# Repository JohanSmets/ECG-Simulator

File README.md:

# ECG-Simulator
 Electronics, Software and 3D Printable Enclosure of the ECG Patient Simulator based on an Atmega328.
 The simulator has 8 selectable heartrates going from 30 to 240 Bpm.  Works with a 9V battery and has an auto power off function.  This project consists of a Full KiCad project with schematic and PCB,  an Arduino sketch and all the 3D-printable files to make an enclosure.

 This project is licensed under Creative Commons Attribution Share-Alike International Licence 4.0

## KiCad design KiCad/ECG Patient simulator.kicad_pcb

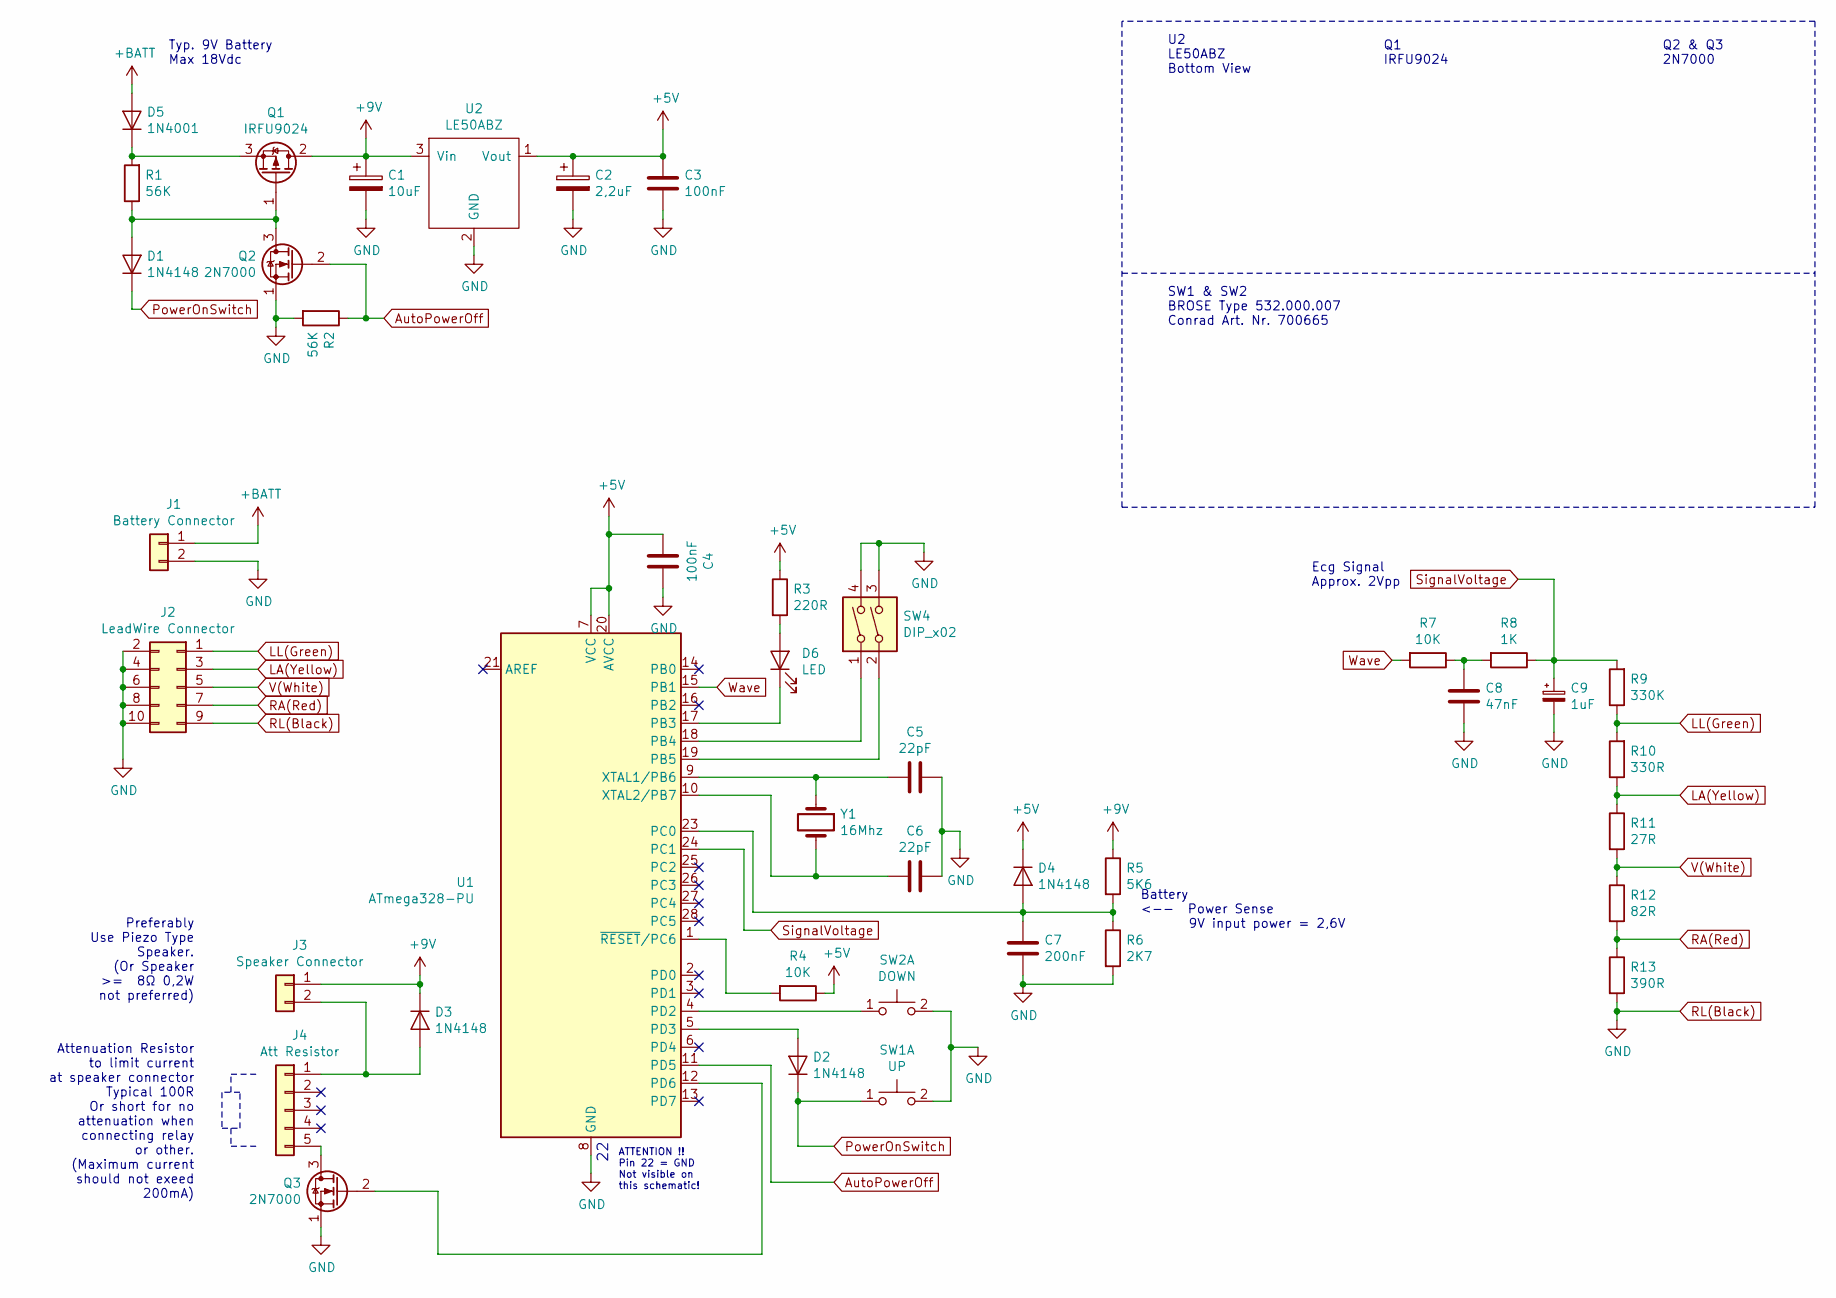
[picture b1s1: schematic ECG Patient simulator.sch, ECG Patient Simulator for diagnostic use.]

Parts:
C1: 10uF; CP_Radial_D6.3mm_P2.50mm
C2: 2,2uF; CP_Radial_D6.3mm_P2.50mm
C3, C4: 100nF; C_Disc_D5.0mm_W2.5mm_P5.00mm
C5, C6: 22pF; C_Disc_D5.0mm_W2.5mm_P5.00mm
C7: 200nF; C_Disc_D5.0mm_W2.5mm_P5.00mm
C8: 47nF; C_Disc_D5.0mm_W2.5mm_P5.00mm
C9: 1uF; CP_Radial_D6.3mm_P2.50mm
D1, D2, D3, D4: 1N4148; D_DO-35_SOD27_P7.62mm_Horizontal
D5: 1N4001; D_DO-41_SOD81_P10.16mm_Horizontal
D6: LED; LED_D5.0mm
J1: Battery Connector; PinHeader_1x02_P2.54mm_Vertical
J2: LeadWire Connector; PinSocket_2x05_P2.54mm_Vertical
J3: Speaker Connector; PinHeader_1x02_P2.54mm_Vertical
J4: Att Resistor; PinHeader_1x05_P2.54mm_Vertical
Q1: IRFU9024; TO-251-3_Vertical
Q2, Q3: 2N7000; TO-92_Inline
R1, R2: 56K; R_Axial_DIN0207_L6.3mm_D2.5mm_P10.16mm_Horizontal
R3: 220R; R_Axial_DIN0207_L6.3mm_D2.5mm_P10.16mm_Horizontal
R4, R7: 10K; R_Axial_DIN0207_L6.3mm_D2.5mm_P10.16mm_Horizontal
R5: 5K6; R_Axial_DIN0207_L6.3mm_D2.5mm_P10.16mm_Horizontal
R6: 2K7; R_Axial_DIN0207_L6.3mm_D2.5mm_P10.16mm_Horizontal
R8: 1K; R_Axial_DIN0207_L6.3mm_D2.5mm_P10.16mm_Horizontal
R9: 330K; R_Axial_DIN0207_L6.3mm_D2.5mm_P10.16mm_Horizontal
R10: 330R; R_Axial_DIN0207_L6.3mm_D2.5mm_P10.16mm_Horizontal
R11: 27R; R_Axial_DIN0207_L6.3mm_D2.5mm_P10.16mm_Horizontal
R12: 82R; R_Axial_DIN0207_L6.3mm_D2.5mm_P10.16mm_Horizontal
R13: 390R; R_Axial_DIN0207_L6.3mm_D2.5mm_P10.16mm_Horizontal
SW1: UP; Push_E-Switch_KS01Q01
SW2: DOWN; Push_E-Switch_KS01Q01
SW4: DIP_x02; DIP-4_W7.62mm
U1: ATmega328-PU; DIP-28_W7.62mm
U2: LE50ABZ; TO-92_Inline_Wide
Y1: 16Mhz; Crystal_HC18-U_Vertical

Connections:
+5V: C2.1, C3.1, C4.2, D4.1 (K), R3.1, R4.1, U1.7 (VCC), U1.20 (AVCC), U2.1 (Vout)
+9V: C1.1, D3.1 (K), J3.1, Q1.2 (D), R5.1, U2.3 (Vin); also elsewhere on the board
+BATT: D5.2 (A), J1.1; also elsewhere on the board
AutoPowerOff: Q2.2 (G), R2.1, U1.11 (PD5)
LA(Yellow): J2.3, R10.1, R11.1
LL(Green): J2.1, R9.1, R10.2
unnamed: C5.2, U1.9 (XTAL1/PB6), Y1.1
unnamed: C6.2, U1.10 (XTAL2/PB7), Y1.2
unnamed: C7.1, D4.2 (A), R5.2, R6.1, U1.23 (PC0)
unnamed: C8.1, R7.1, R8.2
unnamed: D1.2 (A), Q1.1 (G), Q2.3 (D), R1.1
unnamed: D2.2 (A), U1.5 (PD3)
unnamed 12: D3.2 (A), J3.2, J4.1; also elsewhere on the board
unnamed: D5.1 (K), Q1.3 (S), R1.2
unnamed: D6.1 (K), U1.17 (PB3)
unnamed: D6.2 (A), R3.2
unnamed: J4.5, Q3.3 (D)
unnamed: Q3.2 (G), U1.12 (PD6)
unnamed: R4.2, U1.1 (~RESET~/PC6)
unnamed: SW2.1 (C), U1.4 (PD2)
unnamed: SW4.1, U1.18 (PB4)
unnamed: SW4.2, U1.19 (PB5)
PowerOnSwitch: D1.1 (K), D2.1 (K), SW1.1 (C)
RA(Red): J2.7, R12.2, R13.1
RL(Black): C1.2, C2.2, C3.2, C4.1, C5.1, C6.1, C7.2, C8.2, C9.2, J1.2, J2.2, J2.4, J2.6, J2.8, J2.9, J2.10, Q2.1 (S), Q3.1 (S), R2.2, R6.2, R13.2, SW1.2 (D), SW2.2 (D), SW4.3, SW4.4, U1.8 (GND), U1.22 (GND), U2.2 (GND); also elsewhere on the board
SignalVoltage: C9.1, R8.1, R9.2, U1.24 (PC1)
V(White): J2.5, R11.2, R12.1
Wave: R7.2, U1.15 (PB1)

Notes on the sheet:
Battery <-- Power Sense 9V input power = 2,6V
Typ. 9V Battery Max 18Vdc
U2 LE50ABZ Bottom View
Q1 IRFU9024
Q2 & Q3 2N7000
SW1 & SW2 BROSE Type 532.000.007 Conrad Art. Nr. 700665
ATTENTION !! Pin 22 = GND Not visible on this schematic!
Ecg Signal Approx. 2Vpp
Preferably Use Piezo Type Speaker. (Or Speaker >= 8Ω 0,2W not preferred)
Attenuation Resistor to limit current at speaker connector Typical 100R Or short for no attenuation when connecting relay or other. (Maximum current should not exeed 200mA)

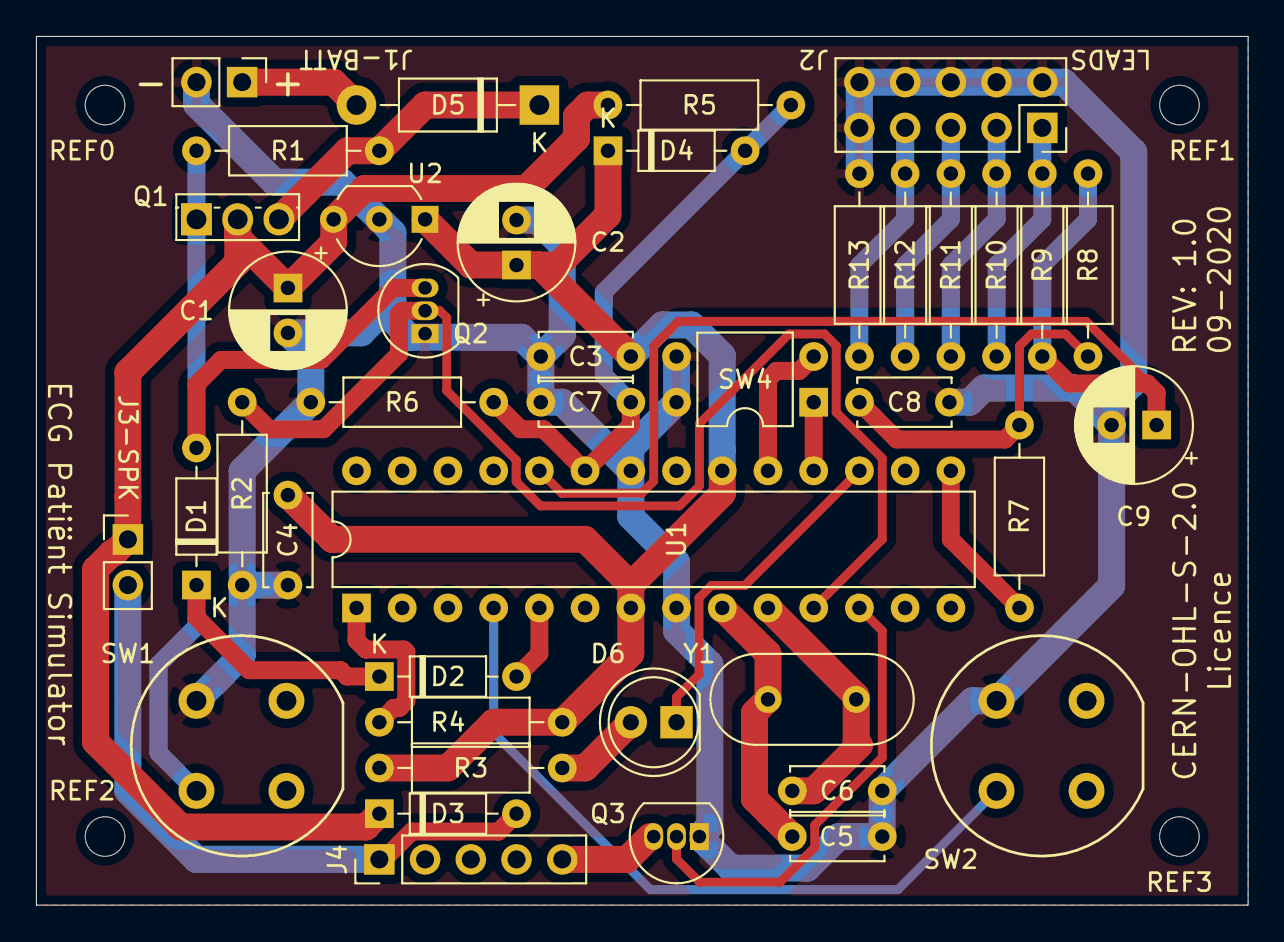
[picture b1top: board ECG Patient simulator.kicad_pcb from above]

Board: 2 copper layers, 67.3 x 48.3 mm, 45 parts (0 on the bottom side), 28 nets.

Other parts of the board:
J1-BATT: Battery Connector; PinHeader_1x02_P2.54mm_Vertical
J3-SPK: Speaker Connector; PinHeader_1x02_P2.54mm_Vertical
REF0, REF1, REF2, REF3: MountingHole_2.2mm_M2_ISO7380

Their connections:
+9V: J3-SPK.1; also elsewhere on the board
+BATT: J1-BATT.1; also elsewhere on the board
unnamed 12: J3-SPK.2; also elsewhere on the board
RL(Black): J1-BATT.2; also elsewhere on the board

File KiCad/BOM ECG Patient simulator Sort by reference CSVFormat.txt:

"Source:","C:\Users\Johan\Documents\Arduino\Projecten\ECG Simulator\KiCad ECG Patient simulator\ECG Patient simulator.sch"
"Date:","14/11/2020 13:45:55"
"Tool:","Eeschema (5.1.0)-1"
"Component Count:","41"
"Ref","Value","Footprint","Datasheet","Manufacturer","Vendor"
"C1","10uF","Capacitor_THT:CP_Radial_D6.3mm_P2.50mm","~","",""
"C2","2,2uF","Capacitor_THT:CP_Radial_D6.3mm_P2.50mm","~","",""
"C3","100nF","Capacitor_THT:C_Disc_D5.0mm_W2.5mm_P5.00mm","~","",""
"C4","100nF","Capacitor_THT:C_Disc_D5.0mm_W2.5mm_P5.00mm","~","",""
"C5","22pF","Capacitor_THT:C_Disc_D5.0mm_W2.5mm_P5.00mm","~","",""
"C6","22pF","Capacitor_THT:C_Disc_D5.0mm_W2.5mm_P5.00mm","~","",""
"C7","200nF","Capacitor_THT:C_Disc_D5.0mm_W2.5mm_P5.00mm","~","",""
"C8","47nF","Capacitor_THT:C_Disc_D5.0mm_W2.5mm_P5.00mm","~","",""
"C9","1uF","Capacitor_THT:CP_Radial_D6.3mm_P2.50mm","~","",""
"D1","1N4148","Diode_THT:D_DO-35_SOD27_P7.62mm_Horizontal","https://assets.nexperia.com/documents/data-sheet/1N4148_1N4448.pdf","",""
"D2","1N4148","Diode_THT:D_DO-35_SOD27_P7.62mm_Horizontal","https://assets.nexperia.com/documents/data-sheet/1N4148_1N4448.pdf","",""
"D3","1N4148","Diode_THT:D_DO-35_SOD27_P7.62mm_Horizontal","~","",""
"D4","1N4148","Diode_THT:D_DO-35_SOD27_P7.62mm_Horizontal","https://assets.nexperia.com/documents/data-sheet/1N4148_1N4448.pdf","",""
"D5","1N4001","Diode_THT:D_DO-41_SOD81_P10.16mm_Horizontal","http://www.vishay.com/docs/88503/1n4001.pdf","",""
"D6","LED","LED_THT:LED_D5.0mm","~","",""
"J1","Battery Connector","Connector_PinHeader_2.54mm:PinHeader_1x02_P2.54mm_Vertical","~","",""
"J2","LeadWire Connector","Connector_PinSocket_2.54mm:PinSocket_2x05_P2.54mm_Vertical","~","",""
"J3","Speaker Connector","Connector_PinHeader_2.54mm:PinHeader_1x02_P2.54mm_Vertical","~","",""
"J4","Att Resistor","Connector_PinHeader_2.54mm:PinHeader_1x05_P2.54mm_Vertical","~","",""
"Q1","IRFU9024","Package_TO_SOT_THT:TO-251-3_Vertical","","",""
"Q2","2N7000","Package_TO_SOT_THT:TO-92_Inline","https://www.fairchildsemi.com/datasheets/2N/2N7000.pdf","",""
"Q3","2N7000","Package_TO_SOT_THT:TO-92_Inline","https://www.fairchildsemi.com/datasheets/2N/2N7000.pdf","",""
"R1","56K","Resistor_THT:R_Axial_DIN0207_L6.3mm_D2.5mm_P10.16mm_Horizontal","~","",""
"R2","56K","Resistor_THT:R_Axial_DIN0207_L6.3mm_D2.5mm_P10.16mm_Horizontal","~","",""
"R3","220R","Resistor_THT:R_Axial_DIN0207_L6.3mm_D2.5mm_P10.16mm_Horizontal","~","",""
"R4","10K","Resistor_THT:R_Axial_DIN0207_L6.3mm_D2.5mm_P10.16mm_Horizontal","~","",""
"R5","5K6","Resistor_THT:R_Axial_DIN0207_L6.3mm_D2.5mm_P10.16mm_Horizontal","~","",""
"R6","2K7","Resistor_THT:R_Axial_DIN0207_L6.3mm_D2.5mm_P10.16mm_Horizontal","~","",""
"R7","10K","Resistor_THT:R_Axial_DIN0207_L6.3mm_D2.5mm_P10.16mm_Horizontal","~","",""
"R8","1K","Resistor_THT:R_Axial_DIN0207_L6.3mm_D2.5mm_P10.16mm_Horizontal","~","",""
"R9","330K","Resistor_THT:R_Axial_DIN0207_L6.3mm_D2.5mm_P10.16mm_Horizontal","~","",""
"R10","330R","Resistor_THT:R_Axial_DIN0207_L6.3mm_D2.5mm_P10.16mm_Horizontal","~","",""
"R11","27R","Resistor_THT:R_Axial_DIN0207_L6.3mm_D2.5mm_P10.16mm_Horizontal","~","",""
"R12","82R","Resistor_THT:R_Axial_DIN0207_L6.3mm_D2.5mm_P10.16mm_Horizontal","~","",""
"R13","390R","Resistor_THT:R_Axial_DIN0207_L6.3mm_D2.5mm_P10.16mm_Horizontal","~","",""
"SW1","UP","Button_Switch_THT:Push_E-Switch_KS01Q01","","",""
"SW2","DOWN","Button_Switch_THT:Push_E-Switch_KS01Q01","","",""
"SW4","DIP_x02","Package_DIP:DIP-4_W7.62mm","~","",""
"U1","ATmega328-PU","Package_DIP:DIP-28_W7.62mm","http://ww1.microchip.com/downloads/en/DeviceDoc/ATmega328_P%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","",""
"U2","LE50ABZ","Package_TO_SOT_THT:TO-92_Inline_Wide","","",""
"Y1","16Mhz","Crystal:Crystal_HC18-U_Vertical","~","",""

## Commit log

2020-12-28 Initialize
    First commit
2020-12-28 Update README.md
    Changed Description
2021-01-01 Added datasheet of MOSFET 2N7000

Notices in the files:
KiCad/ECG Patient simulator.kicad_pcb:
CERN-OHL-S-2.0
KiCad/ECG Patient simulator.sch:
Copyright Johan Smets 2020.
CC-BY-SA licence.
under the terms of the CERN-OHL-S-2.0 licence or any later version and under the
